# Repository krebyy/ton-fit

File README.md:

Ton-Fit V2.0
========

The Ton-Fit V2.0 Board is a development and prototyping platform based on the ARM Cortex-M4 32-bit microcontroller [STM32F405](http://www.st.com/en/microcontrollers/stm32f405rg.html).

# License

Copyright Kleber Lima da Silva 2018.

This documentation describes Open Hardware and is licensed under the CERN OHL v. 1.2.
You may redistribute and modify this documentation under the terms of the CERN OHL v.1.2. (http://ohwr.org/cernohl). This documentation is distributed WITHOUT ANY EXPRESS OR IMPLIED WARRANTY, INCLUDING OF MERCHANTABILITY, SATISFACTORY QUALITY AND FITNESS FOR A PARTICULAR PURPOSE. Please see the CERN OHL v.1.2 for applicable conditions.

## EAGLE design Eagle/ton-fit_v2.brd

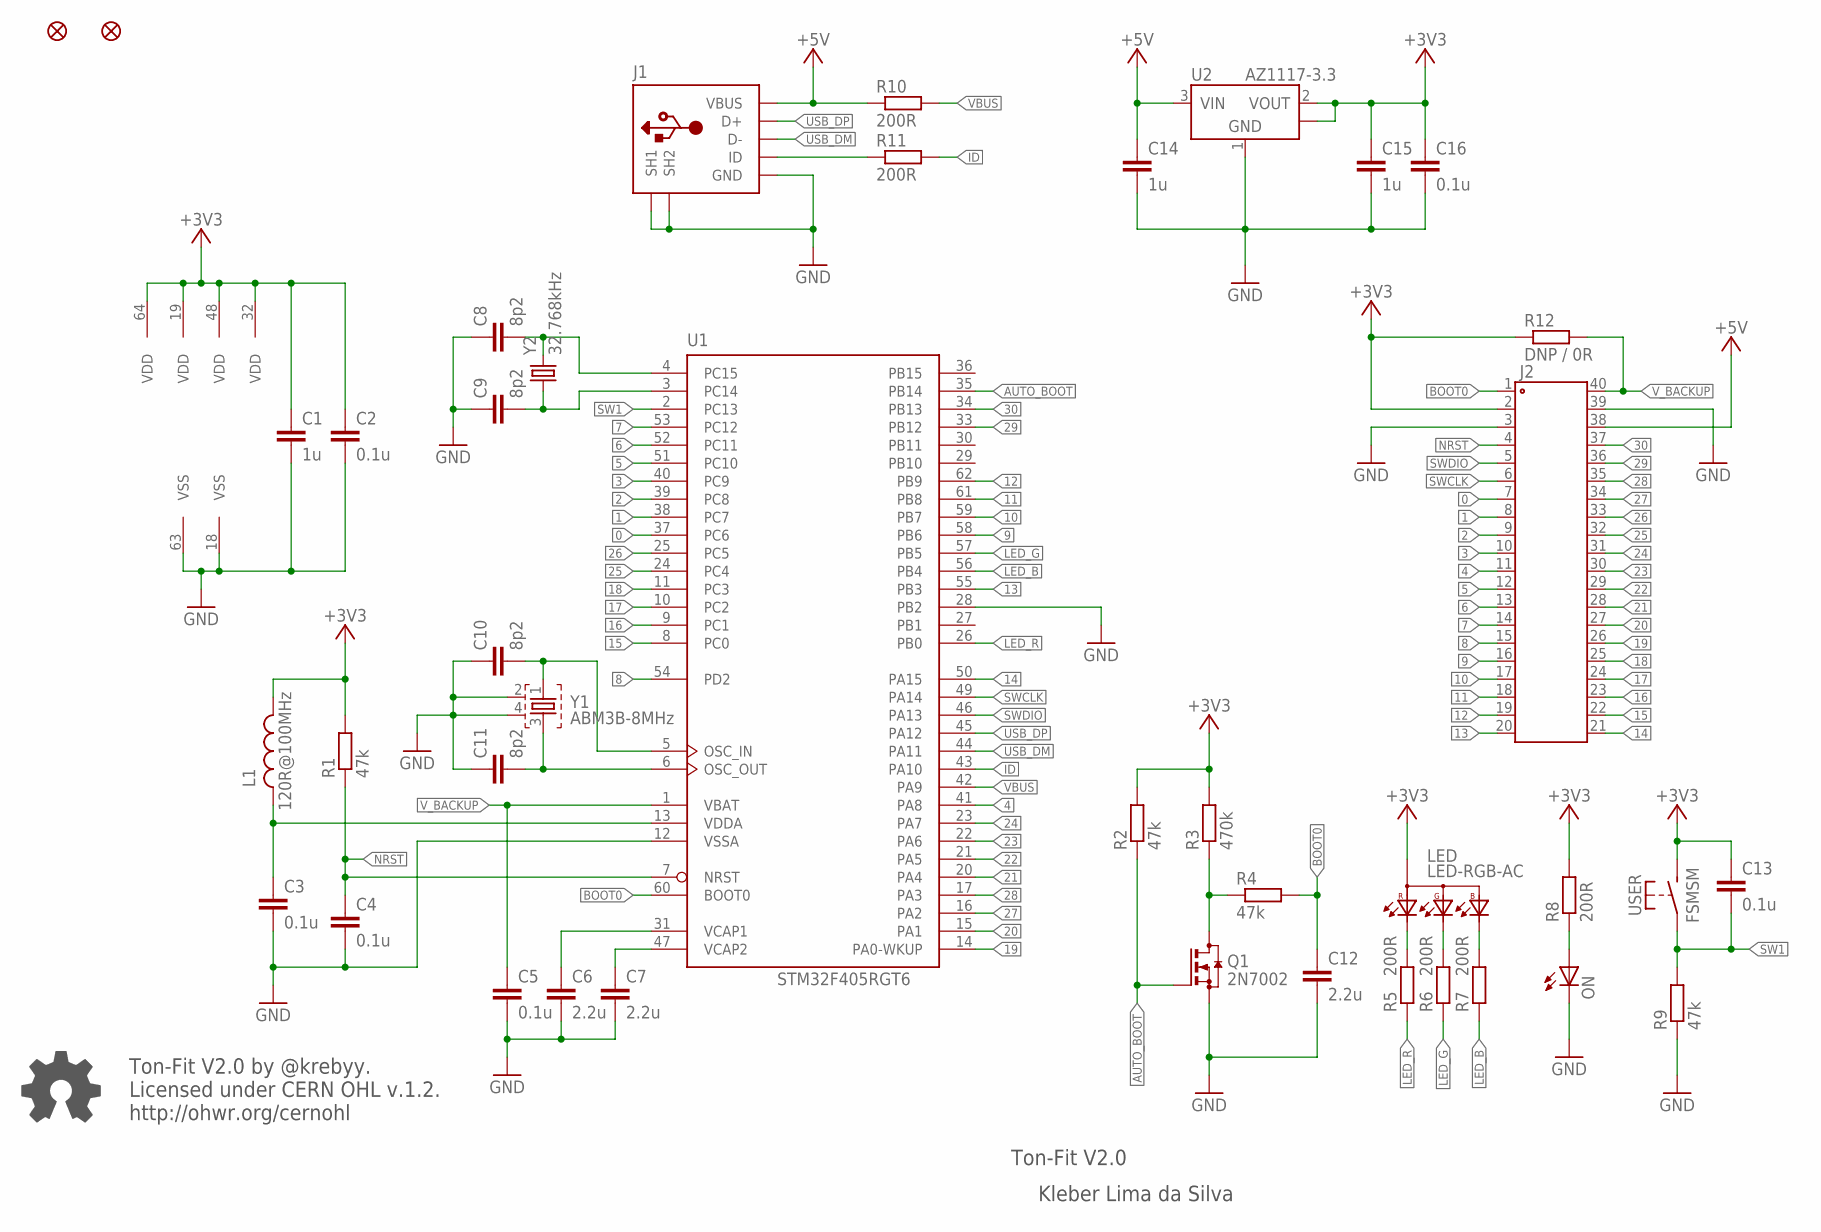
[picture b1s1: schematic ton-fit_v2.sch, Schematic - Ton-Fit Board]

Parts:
C1, C14, C15: 1u; C0603
C2, C3, C4, C5, C13, C16: 0.1u; C0603
C6, C7, C12: 2.2u; C0603
C8, C9, C10, C11: 8p2; C0603
FIDUCIAL1, FIDUCIAL2: FIDUCIAL; FIDUCIAL-1X2
J1: USBR; 0475890001
J2: DIL40
L1: 120R@100MHz; L0603
LED: LED-RGB-AC; 0606
ON: LEDCHIPLED_0603; CHIPLED_0603
Q1: 2N7002; SOT23
R1, R2, R4, R9: 47k; R0603
R3: 470k; R0603
R5, R6, R7, R8, R10, R11: 200R; R0603
R12: DNP / 0R; R0603
U1: STM32F405RGT6; LQFP64
U2: AZ1117-3.3; SOT223
USER: FSMSM
Y1: ABM3B-8MHz; ABM3B
Y2: 32.768kHz; 3.2X1.5

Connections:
0: J2.7, U1.37 (PC6)
1: J2.8, U1.38 (PC7)
2: J2.9, U1.39 (PC8)
3: J2.10, U1.40 (PC9)
4: J2.11, U1.41 (PA8)
5: J2.12, U1.51 (PC10)
6: J2.13, U1.52 (PC11)
7: J2.14, U1.53 (PC12)
8: J2.15, U1.54 (PD2)
9: J2.16, U1.58 (PB6)
10: J2.17, U1.59 (PB7)
11: J2.18, U1.61 (PB8)
12: J2.19, U1.62 (PB9)
13: J2.20, U1.55 (PB3)
14: J2.21, U1.50 (PA15)
15: J2.22, U1.8 (PC0)
16: J2.23, U1.9 (PC1)
17: J2.24, U1.10 (PC2)
18: J2.25, U1.11 (PC3)
19: J2.26, U1.14 (PA0-WKUP)
20: J2.27, U1.15 (PA1)
21: J2.28, U1.20 (PA4)
22: J2.29, U1.21 (PA5)
23: J2.30, U1.22 (PA6)
24: J2.31, U1.23 (PA7)
25: J2.32, U1.24 (PC4)
26: J2.33, U1.25 (PC5)
27: J2.34, U1.16 (PA2)
28: J2.35, U1.17 (PA3)
29: J2.36, U1.33 (PB12)
30: J2.37, U1.34 (PB13)
+3V3: C1.1, C2.1, C13.1, C15.1, C16.1, J2.2, L1.1, LED.4 (A), R1.2, R2.2, R3.2, R8.2, R12.1, U1.19 (VDD), U1.32 (VDD), U1.48 (VDD), U1.64 (VDD), U2.2 (VOUT), U2.4 (TAB), USER.2
+5V: C14.1, J1.1 (VBUS), J2.38, R10.1, U2.3 (VIN)
AUTO_BOOT: Q1.1 (G), R2.1, U1.35 (PB14)
BOOT0: C12.1, J2.1, R4.2, U1.60 (BOOT0)
GND: C1.2, C2.2, C3.2, C4.2, C5.2, C6.2, C7.2, C8.1, C9.1, C10.1, C11.1, C12.2, C14.2, C15.2, C16.2, J1.5 (GND), J1.SH1, J1.SH2 (SH1), J1.SH3 (SH2), J1.SH4 (SH2), J1.SH5 (SH1), J1.SH6 (SH2), J2.3, J2.39, ON.C, Q1.2 (S), R9.1, U1.12 (VSSA), U1.18 (VSS), U1.28 (PB2), U1.63 (VSS), U2.1 (GND), Y1.2, Y1.4
ID: R11.2, U1.43 (PA10)
LED_B: R7.1, U1.56 (PB4)
LED_G: R6.1, U1.57 (PB5)
LED_R: R5.1, U1.26 (PB0)
unnamed: C10.2, U1.5 (OSC_IN), Y1.1
unnamed: C11.2, U1.6 (OSC_OUT), Y1.3
unnamed: ON.A, R8.1
unnamed: LED.1 (KRED), R5.2
unnamed: C6.1, U1.31 (VCAP1)
unnamed: C7.1, U1.47 (VCAP2)
unnamed: LED.2 (KGREEN), R6.2
unnamed: LED.3 (KBLUE), R7.2
unnamed: C3.1, L1.2, U1.13 (VDDA)
unnamed: C8.2, U1.4 (PC15), Y2.2
unnamed: Q1.3 (D), R3.1, R4.1
unnamed: C9.2, U1.3 (PC14), Y2.1
NRST: C4.1, J2.4, R1.1, U1.7 (NRST)
SW1: C13.2, R9.2, U1.2 (PC13), USER.1
SWCLK: J2.6, U1.49 (PA14)
SWDIO: J2.5, U1.46 (PA13)
USB_DM: J1.2 (D-), U1.44 (PA11)
USB_DP: J1.3 (D+), U1.45 (PA12)
USB_ID: J1.4 (ID), R11.1
VBUS: R10.2, U1.42 (PA9)
V_BACKUP: C5.1, J2.40, R12.2, U1.1 (VBAT)

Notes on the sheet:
Ton-Fit V2.0 by @krebyy. Licensed under CERN OHL v.1.2. http://ohwr.org/cernohl
Ton-Fit V2.0
Kleber Lima da Silva

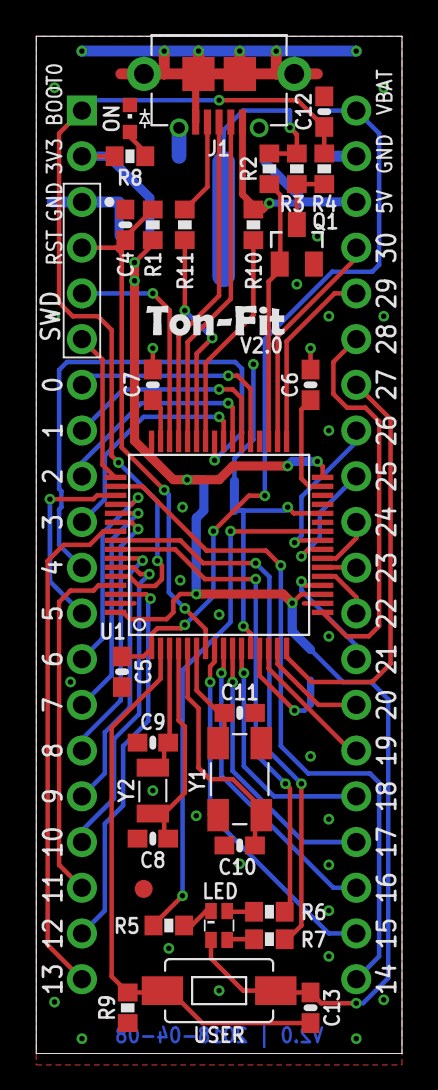
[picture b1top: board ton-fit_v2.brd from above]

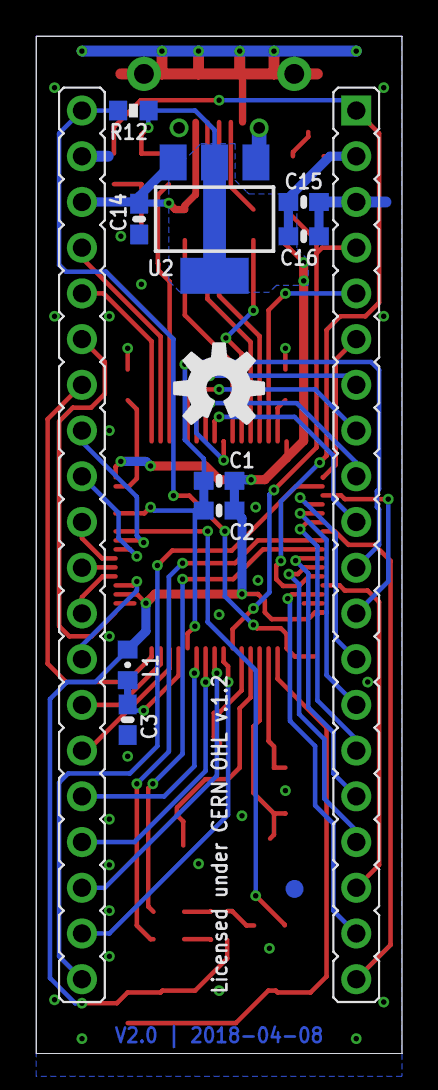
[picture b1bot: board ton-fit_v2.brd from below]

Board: 2 copper layers, 20.3 x 56.5 mm, 42 parts (11 on the bottom side), 61 nets.

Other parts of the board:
U$1: OSHW-LOGO-M

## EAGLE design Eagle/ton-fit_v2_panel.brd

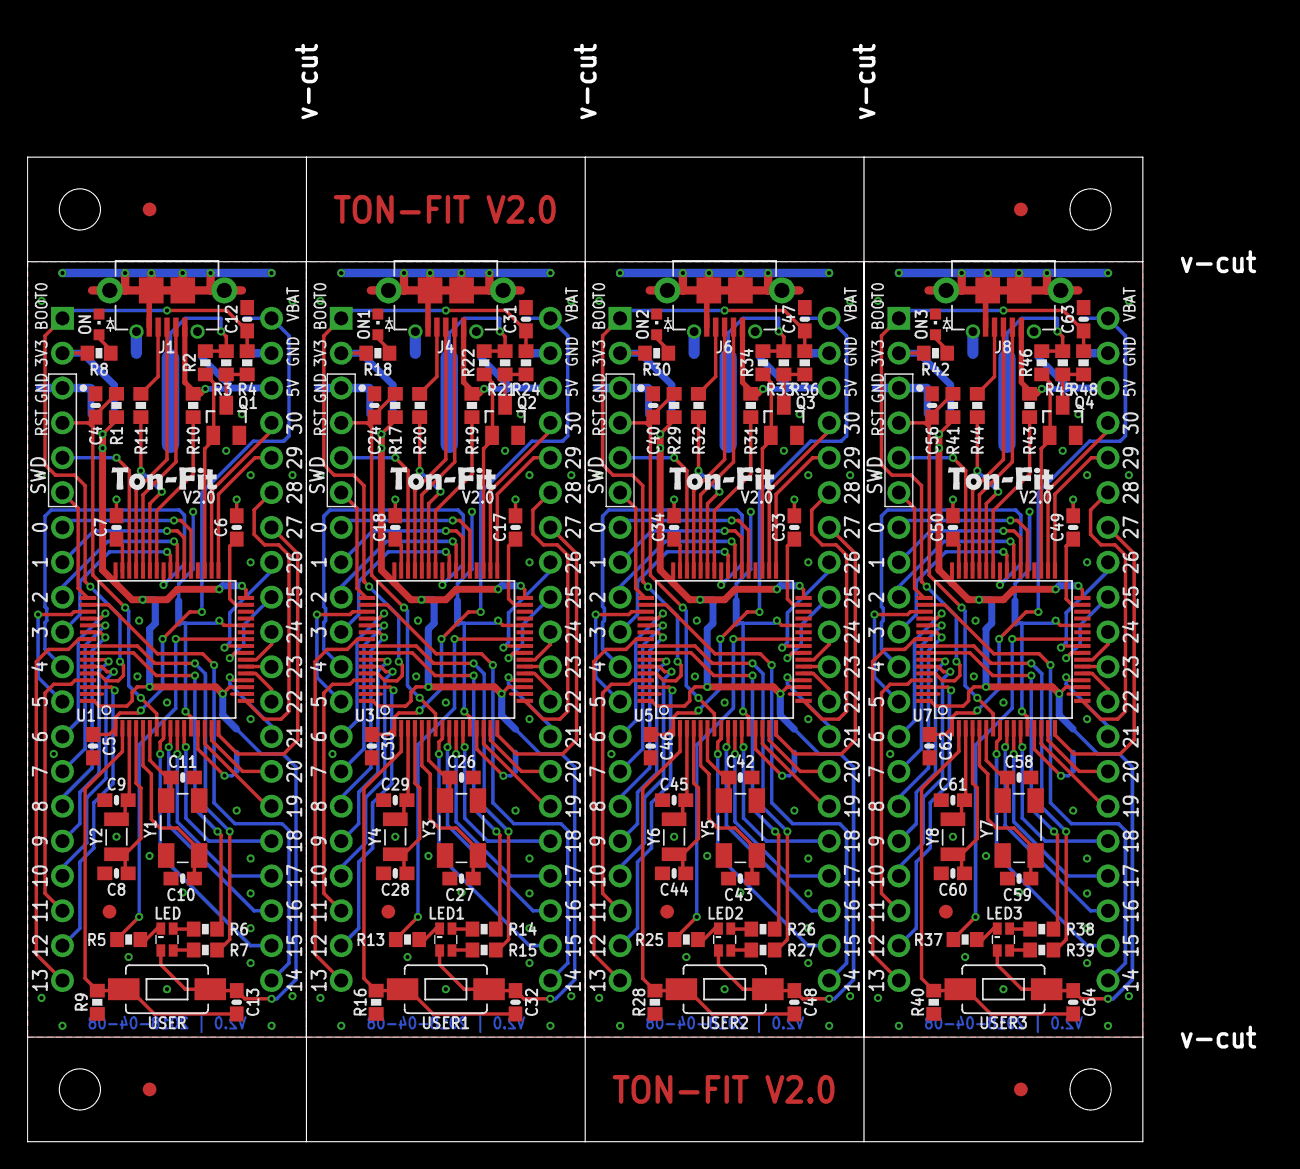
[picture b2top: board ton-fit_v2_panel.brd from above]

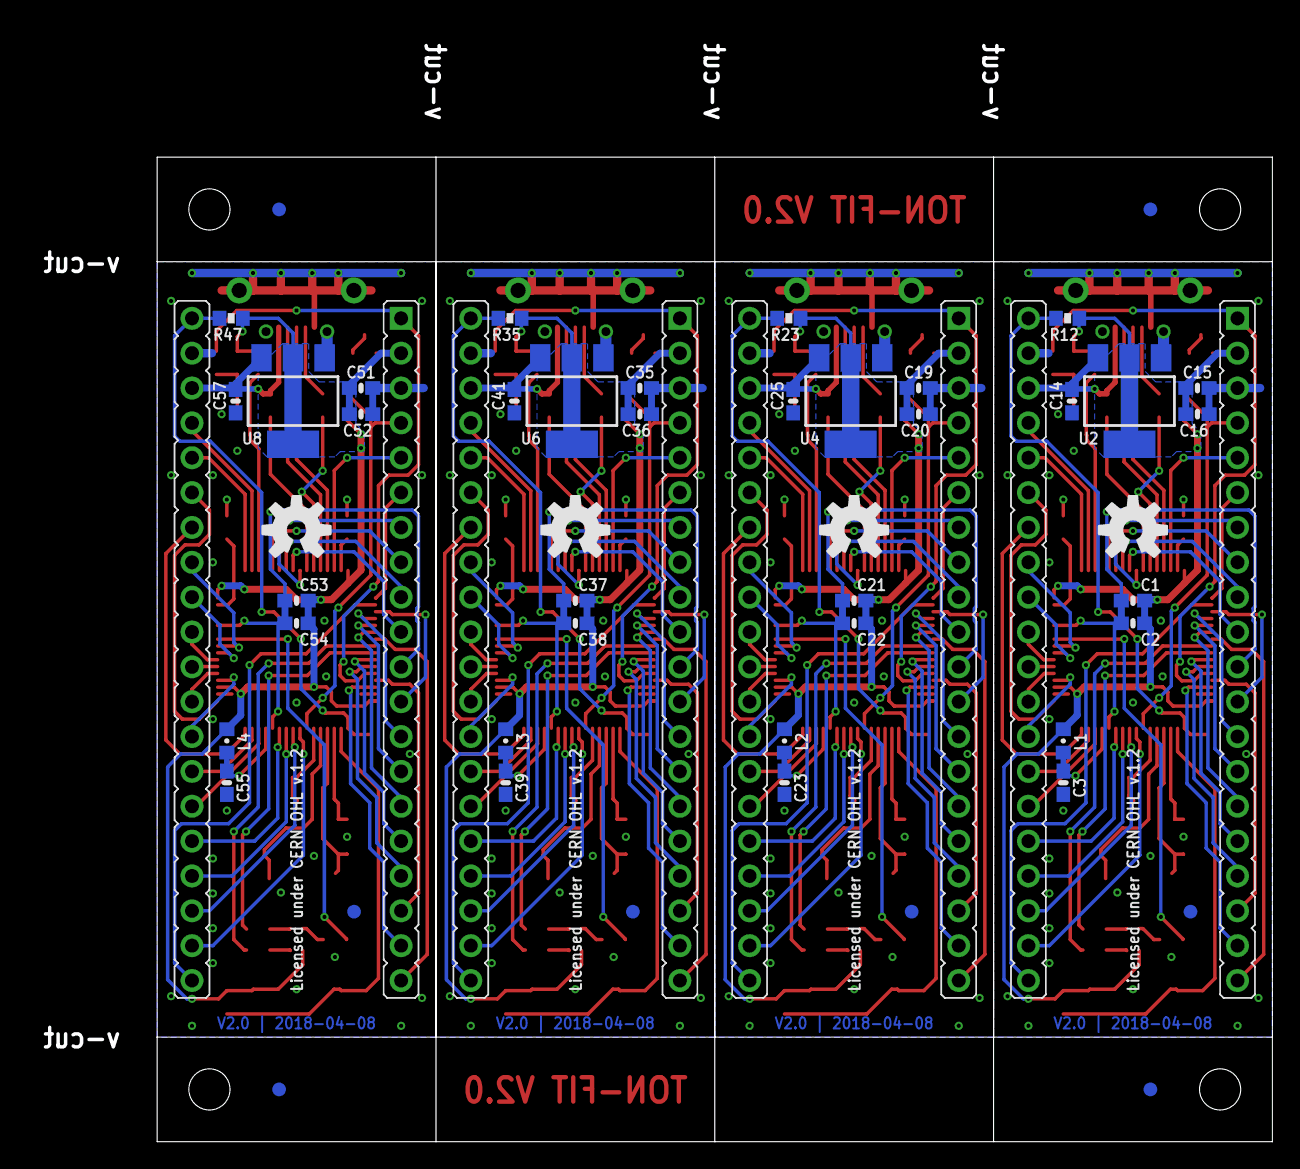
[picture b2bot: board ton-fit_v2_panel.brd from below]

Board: 2 copper layers, 81.3 x 71.8 mm, 176 parts (48 on the bottom side), 244 nets.

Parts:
C1, C14, C15, C19, C21, C25, C35, C37, C41, C51, C53, C57: 1u; C0603
C2, C3, C4, C5, C13, C16, C20, C22, C23, C24, C30, C32, C36, C38, C39, C40, C46, C48, C52, C54, C55, C56, C62, C64: 0.1u; C0603
C6, C7, C12, C17, C18, C31, C33, C34, C47, C49, C50, C63: 2.2u; C0603
C8, C9, C10, C11, C26, C27, C28, C29, C42, C43, C44, C45, C58, C59, C60, C61: 8p2; C0603
E$1, E$2, E$3, E$4, E$5, E$6, E$7, E$8: FIDUCIAL-1X2
FIDUCIAL1, FIDUCIAL2, FIDUCIAL3, FIDUCIAL4, FIDUCIAL5, FIDUCIAL6, FIDUCIAL7, FIDUCIAL8: FIDUCIAL; FIDUCIAL-1X2
J1, J4, J6, J8: 0475890001
J2, J3, J5, J7: DIL40
L1, L2, L3, L4: 120R@100MHz; L0603
LED, LED1, LED2, LED3: LED-RGB-AC; 0606
ON, ON1, ON2, ON3: CHIPLED_0603
Q1, Q2, Q3, Q4: 2N7002; SOT23
R1, R2, R4, R9, R16, R17, R22, R24, R28, R29, R34, R36, R40, R41, R46, R48: 47k; R0603
R3, R21, R33, R45: 470k; R0603
R5, R6, R7, R8, R10, R11, R13, R14, R15, R18, R19, R20, R25, R26, R27, R30, R31, R32, R37, R38, R39, R42, R43, R44: 200R; R0603
R12, R23, R35, R47: DNP / 0R; R0603
U1, U3, U5, U7: STM32F405RGT6; LQFP64
U2, U4, U6, U8: AZ1117-3.3; SOT223
U$1, U$2, U$3, U$4: OSHW-LOGO-M
USER, USER1, USER2, USER3: FSMSM
Y1, Y3, Y5, Y7: ABM3B-8MHz; ABM3B
Y2, Y4, Y6, Y8: 32.768kHz; 3.2X1.5

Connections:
0: J2.7, U1.37
1: J2.8, U1.38
2: J2.9, U1.39
3: J2.10, U1.40
4: J2.11, U1.41
5: J2.12, U1.51
6: J2.13, U1.52
7: J2.14, U1.53
8: J2.15, U1.54
9: J2.16, U1.58
10: J2.17, U1.59
11: J2.18, U1.61
12: J2.19, U1.62
13: J2.20, U1.55
14: J2.21, U1.50
15: J2.22, U1.8
16: J2.23, U1.9
17: J2.24, U1.10
18: J2.25, U1.11
19: J2.26, U1.14
20: J2.27, U1.15
21: J2.28, U1.20
22: J2.29, U1.21
23: J2.30, U1.22
24: J2.31, U1.23
25: J2.32, U1.24
26: J2.33, U1.25
27: J2.34, U1.16
28: J2.35, U1.17
29: J2.36, U1.33
30: J2.37, U1.34
31: J3.12, U3.51
32: J3.17, U3.59
33: J3.16, U3.58
34: J3.15, U3.54
35: J3.14, U3.53
36: J3.13, U3.52
37: J3.8, U3.38
38: J3.7, U3.37
39: J3.36, U3.33
40: J3.35, U3.17
41: J3.34, U3.16
42: J3.33, U3.25
43: J3.32, U3.24
44: J3.31, U3.23
45: J3.30, U3.22
46: J3.29, U3.21
47: J3.28, U3.20
48: J3.27, U3.15
49: J3.26, U3.14
50: J3.25, U3.11
51: J3.24, U3.10
52: J3.9, U3.39
53: J3.10, U3.40
54: J3.11, U3.41
55: J3.18, U3.61
56: J3.19, U3.62
57: J3.20, U3.55
58: J3.21, U3.50
59: J3.22, U3.8
60: J3.23, U3.9
61: J3.37, U3.34
62: J5.12, U5.51
63: J5.17, U5.59
64: J5.16, U5.58
65: J5.15, U5.54
66: J5.14, U5.53
67: J5.13, U5.52
68: J5.8, U5.38
69: J5.7, U5.37
70: J5.36, U5.33
71: J5.35, U5.17
72: J5.34, U5.16
73: J5.33, U5.25
74: J5.32, U5.24
75: J5.31, U5.23
76: J5.30, U5.22
77: J5.29, U5.21
78: J5.28, U5.20
79: J5.27, U5.15
80: J5.26, U5.14
81: J5.25, U5.11
82: J5.24, U5.10
83: J5.9, U5.39
84: J5.10, U5.40
85: J5.11, U5.41
86: J5.18, U5.61
87: J5.19, U5.62
88: J5.20, U5.55
89: J5.21, U5.50
90: J5.22, U5.8
91: J5.23, U5.9
92: J5.37, U5.34
93: J7.12, U7.51
94: J7.17, U7.59
95: J7.16, U7.58
96: J7.15, U7.54
97: J7.14, U7.53
98: J7.13, U7.52
99: J7.8, U7.38
100: J7.7, U7.37
101: J7.36, U7.33
102: J7.35, U7.17
103: J7.34, U7.16
104: J7.33, U7.25
105: J7.32, U7.24
106: J7.31, U7.23
107: J7.30, U7.22
108: J7.29, U7.21
109: J7.28, U7.20
110: J7.27, U7.15
111: J7.26, U7.14
112: J7.25, U7.11
113: J7.24, U7.10
114: J7.9, U7.39
115: J7.10, U7.40
116: J7.11, U7.41
117: J7.18, U7.61
118: J7.19, U7.62
119: J7.20, U7.55
120: J7.21, U7.50
121: J7.22, U7.8
122: J7.23, U7.9
123: J7.37, U7.34
+3V1: C19.1, C20.1, C21.1, C22.1, C32.1, J3.2, L2.1, LED1.4, R17.2, R18.2, R21.2, R22.2, R23.1, U3.19, U3.32, U3.48, U3.64, U4.2, U4.4, USER1.2
+3V2: C35.1, C36.1, C37.1, C38.1, C48.1, J5.2, L3.1, LED2.4, R29.2, R30.2, R33.2, R34.2, R35.1, U5.19, U5.32, U5.48, U5.64, U6.2, U6.4, USER2.2
+3V3: C1.1, C2.1, C13.1, C15.1, C16.1, J2.2, L1.1, LED.4, R1.2, R2.2, R3.2, R8.2, R12.1, U1.19, U1.32, U1.48, U1.64, U2.2, U2.4, USER.2
+3V4: C51.1, C52.1, C53.1, C54.1, C64.1, J7.2, L4.1, LED3.4, R41.2, R42.2, R45.2, R46.2, R47.1, U7.19, U7.32, U7.48, U7.64, U8.2, U8.4, USER3.2
+5V: C14.1, J1.1, J2.38, R10.1, U2.3
+5V1: C25.1, J3.38, J4.1, R19.1, U4.3
+5V2: C41.1, J5.38, J6.1, R31.1, U6.3
+5V3: C57.1, J7.38, J8.1, R43.1, U8.3
AUTO_BOOT: Q1.1, R2.1, U1.35
AUTO_BOOT1: Q2.1, R22.1, U3.35
AUTO_BOOT2: Q3.1, R34.1, U5.35
AUTO_BOOT3: Q4.1, R46.1, U7.35
BOOT0: C12.1, J2.1, R4.2, U1.60
BOOT1: C31.1, J3.1, R24.2, U3.60
BOOT2: C47.1, J5.1, R36.2, U5.60
BOOT3: C63.1, J7.1, R48.2, U7.60
GND: C1.2, C2.2, C3.2, C4.2, C5.2, C6.2, C7.2, C8.1, C9.1, C10.1, C11.1, C12.2, C14.2, C15.2, C16.2, J1.5, J1.SH1, J1.SH2, J1.SH3, J1.SH4, J1.SH5, J1.SH6, J2.3, J2.39, ON.C, Q1.2, R9.1, U1.12, U1.18, U1.28, U1.63, U2.1, Y1.2, Y1.4
GND1: C17.2, C18.2, C19.2, C20.2, C21.2, C22.2, C23.2, C24.2, C25.2, C26.1, C27.1, C28.1, C29.1, C30.2, C31.2, J3.3, J3.39, J4.5, J4.SH1, J4.SH2, J4.SH3, J4.SH4, J4.SH5, J4.SH6, ON1.C, Q2.2, R16.1, U3.12, U3.18, U3.28, U3.63, U4.1, Y3.2, Y3.4
GND2: C33.2, C34.2, C35.2, C36.2, C37.2, C38.2, C39.2, C40.2, C41.2, C42.1, C43.1, C44.1, C45.1, C46.2, C47.2, J5.3, J5.39, J6.5, J6.SH1, J6.SH2, J6.SH3, J6.SH4, J6.SH5, J6.SH6, ON2.C, Q3.2, R28.1, U5.12, U5.18, U5.28, U5.63, U6.1, Y5.2, Y5.4
GND3: C49.2, C50.2, C51.2, C52.2, C53.2, C54.2, C55.2, C56.2, C57.2, C58.1, C59.1, C60.1, C61.1, C62.2, C63.2, J7.3, J7.39, J8.5, J8.SH1, J8.SH2, J8.SH3, J8.SH4, J8.SH5, J8.SH6, ON3.C, Q4.2, R40.1, U7.12, U7.18, U7.28, U7.63, U8.1, Y7.2, Y7.4
ID: R11.2, U1.43
ID1: R20.2, U3.43
ID2: R32.2, U5.43
ID3: R44.2, U7.43
LED_B: R7.1, U1.56
LED_B1: R15.1, U3.56
LED_B2: R27.1, U5.56
LED_B3: R39.1, U7.56
LED_G: R6.1, U1.57
LED_G1: R14.1, U3.57
LED_G2: R26.1, U5.57
LED_G3: R38.1, U7.57
LED_R: R5.1, U1.26
LED_R1: R13.1, U3.26
LED_R2: R25.1, U5.26
LED_R3: R37.1, U7.26
unnamed: C10.2, U1.5, Y1.1
unnamed: C11.2, U1.6, Y1.3
unnamed: ON.A, R8.1
unnamed: LED.1, R5.2
unnamed: C6.1, U1.31
unnamed: C7.1, U1.47
unnamed: LED.2, R6.2
unnamed: LED.3, R7.2
unnamed: C3.1, L1.2, U1.13
unnamed: C17.1, U3.31
unnamed: C8.2, U1.4, Y2.2
unnamed: Q1.3, R3.1, R4.1
unnamed: C18.1, U3.47
unnamed: LED1.1, R13.2
unnamed: C9.2, U1.3, Y2.1
unnamed: LED1.2, R14.2
unnamed: LED1.3, R15.2
unnamed: C23.1, L2.2, U3.13
unnamed: ON1.A, R18.1
unnamed: C27.2, U3.5, Y3.1
unnamed: C26.2, U3.6, Y3.3
unnamed: C28.2, U3.4, Y4.2
unnamed: C29.2, U3.3, Y4.1
unnamed: Q2.3, R21.1, R24.1
unnamed: C33.1, U5.31
unnamed: C34.1, U5.47
unnamed: LED2.1, R25.2
unnamed: LED2.2, R26.2
unnamed: LED2.3, R27.2
unnamed: C39.1, L3.2, U5.13
unnamed: ON2.A, R30.1
unnamed: C43.2, U5.5, Y5.1
unnamed: C42.2, U5.6, Y5.3
unnamed: C44.2, U5.4, Y6.2
unnamed: C45.2, U5.3, Y6.1
unnamed: Q3.3, R33.1, R36.1
unnamed: C49.1, U7.31
unnamed: C50.1, U7.47
unnamed: LED3.1, R37.2
unnamed: LED3.2, R38.2
unnamed: LED3.3, R39.2
unnamed: C55.1, L4.2, U7.13
unnamed: ON3.A, R42.1
unnamed: C59.2, U7.5, Y7.1
unnamed: C58.2, U7.6, Y7.3
unnamed: C60.2, U7.4, Y8.2
unnamed: C61.2, U7.3, Y8.1
unnamed: Q4.3, R45.1, R48.1
NRST: C4.1, J2.4, R1.1, U1.7
NRST1: C24.1, J3.4, R17.1, U3.7
NRST2: C40.1, J5.4, R29.1, U5.7
NRST3: C56.1, J7.4, R41.1, U7.7
SW1: C13.2, R9.2, U1.2, USER.1
SW2: C32.2, R16.2, U3.2, USER1.1
SW3: C48.2, R28.2, U5.2, USER2.1
SW4: C64.2, R40.2, U7.2, USER3.1
SWCLK: J2.6, U1.49
SWCLK1: J3.6, U3.49
SWCLK2: J5.6, U5.49
SWCLK3: J7.6, U7.49
SWDIO: J2.5, U1.46
SWDIO1: J3.5, U3.46
SWDIO2: J5.5, U5.46
SWDIO3: J7.5, U7.46
USB_DM: J1.2, U1.44
USB_DM1: J4.2, U3.44
USB_DM2: J6.2, U5.44
USB_DM3: J8.2, U7.44
USB_DP: J1.3, U1.45
USB_DP1: J4.3, U3.45
USB_DP2: J6.3, U5.45
USB_DP3: J8.3, U7.45
USB_ID: J1.4, R11.1
USB_ID1: J4.4, R20.1
USB_ID2: J6.4, R32.1
USB_ID3: J8.4, R44.1
VBUS: R10.2, U1.42
VBUS1: R19.2, U3.42
VBUS2: R31.2, U5.42
VBUS3: R43.2, U7.42
V_BACKUP: C5.1, J2.40, R12.2, U1.1
V_BACKUP1: C30.1, J3.40, R23.2, U3.1
V_BACKUP2: C46.1, J5.40, R35.2, U5.1
V_BACKUP3: C62.1, J7.40, R47.2, U7.1

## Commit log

2018-04-11 First commit - Board V2.0
2018-04-11 Rename schematic pdf
2018-04-11 Cosmetic
2018-04-24 Fix BOM - U2 part number

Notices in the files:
parts and their libraries:
SparkFun: Licensing: CC v3.0 Share-Alike You are welcome to use this library for commercial purposes.
